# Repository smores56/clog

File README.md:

The Clog Family
===============

The Clog is a split 34-key keyboard with pinky clusters, the split version of [the
Osprette][osprette]. It grew its own revisions from there, and they all share the
same layout and firmware, so they live in one repo now, a folder per board:

- [Clog][v1] (`v1`): the original split. Pro-micro compatible, wired or bluetooth
- [Clog V2][v2] (`v2`): wireless-only, on a Seeeduino Xiao BLE, with splay and a roller
- [Clog V3][v3] (`v3`): pro-micro compatible, solder or hotswap
- [Clog V4][v4] (`v4`): hotswap with a switch plate, on a Xiao
- [Steel Toe][steel-toe] (`steel-toe`): BoardSource's V3-derived board
- [Sephirette][sephirette] (`sephirette`): MX-switch split, matching the Osprette MX

Each folder has its own README with ordering details and pictures.

Every board across both families is listed at [smores56/keyboards][index].

# Firmware

The pro-micro boards (Clog, V3, Steel Toe and Sephirette) share a matrix, so they
all run the same firmware: `clog` in QMK and the `clog` shield in ZMK. Clog V2 is
wireless-only and has its own ZMK config, and V4 runs the `geta` shield. My
personal keymaps live in [qmk_userspace][qmk_userspace] and [zmk-config][zmk-config].

# Building

Most of these boards use my [smores.pretty][smores-pretty] KiCad library as a
submodule, so clone with `--recurse-submodules`. The original Clog and the
Sephirette instead pull in Foostan's `kbd` and Daprice's `keyswitches.pretty`.

The unibody half of the family is [the Osprette][osprette].

[osprette]: https://github.com/smores56/osprette
[v1]: ./v1
[v2]: ./v2
[v3]: ./v3
[v4]: ./v4
[steel-toe]: ./steel-toe
[sephirette]: ./sephirette
[qmk_userspace]: https://github.com/smores56/qmk_userspace
[zmk-config]: https://github.com/smores56/zmk-config
[smores-pretty]: https://github.com/smores56/smores.pretty
[index]: https://github.com/smores56/keyboards

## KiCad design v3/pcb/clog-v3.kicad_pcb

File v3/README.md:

The Clog V3
===========

The Clog V3 is a 34-key split keyboard. It has the following features:

- Choc V1 switches (solder or hotswap)
- Wireless or wired only with any Pro Micro-compatible controller
- Pinky clusters (top pinky keys on the sides)
- Splay (4° between middle and ring, 8° between ring and pinky)
- SplitKB puck support for tenting

## How to Order

The [PCB gerber](./gerber/clog-v3.zip) and [plate gerber](./gerber/clog-v3-plate.zip)
have everything you'll need to get this printed.
You can order from [JLC](https://jlcpcb.com) by just uploading that ZIP archive and keeping
the default options. I'd suggest removing the order number, otherwise they'll put
one on the board somewhere randomly.

## Building

### Parts Needed

Part Name            | Quantity        | Notes                                    | Link
--------------------:|:---------------:|:----------------------------------------:|:----
PCB                  | 2 (halves)      |                                          | [JLC](https://jlcpcb.com)
Choc V1 Switches     | 34              |                                          | <https://mkultra.click/choc-switches>
Choc Keycaps         | 34              |                                          | <https://mkultra.click/mbk-factory-colors>
SMD Diodes           | 34              |                                          | <https://www.aliexpress.com/item/3256802562651339.html>
Power Switches       | 2               | Technically optional                     | <https://www.digikey.com/en/products/detail/nidec-copal-electronics/CUS-12TB/1124222>
Pro Micro Controller | 2               | Not technically optional                 | <https://www.boardsource.xyz/products/blok>
Small LiPo Batteries | 2               |                                          | <https://www.aliexpress.com/item/2251832610867849.html>
Inch of Copper Wire  | 1               | Use thin and sheathed                    | Any hardware store
MCU Sockets          | 1 strip to chop | Optional                                 | <https://www.digikey.com/en/products/detail/mill-max-manufacturing-corp/316-43-164-41-006000/1212147>
MCU Socket Pins      | 28              | Optional, buy extras, these are slippery | <https://www.digikey.com/en/products/detail/mill-max-manufacturing-corp/3320-0-00-15-00-00-03-0/4147392>

### Tips

I'd solder the parts in this order:

- Diodes
- Power switches
- MCU sockets/Headers for the Pro Micro's
- MCU pins if you're [socketing](https://docs.splitkb.com/hc/en-us/articles/360011263059-How-do-I-socket-a-microcontroller-)
- Batteries (To the +ve and -ve terminals)
- Choc switches

## Pictures

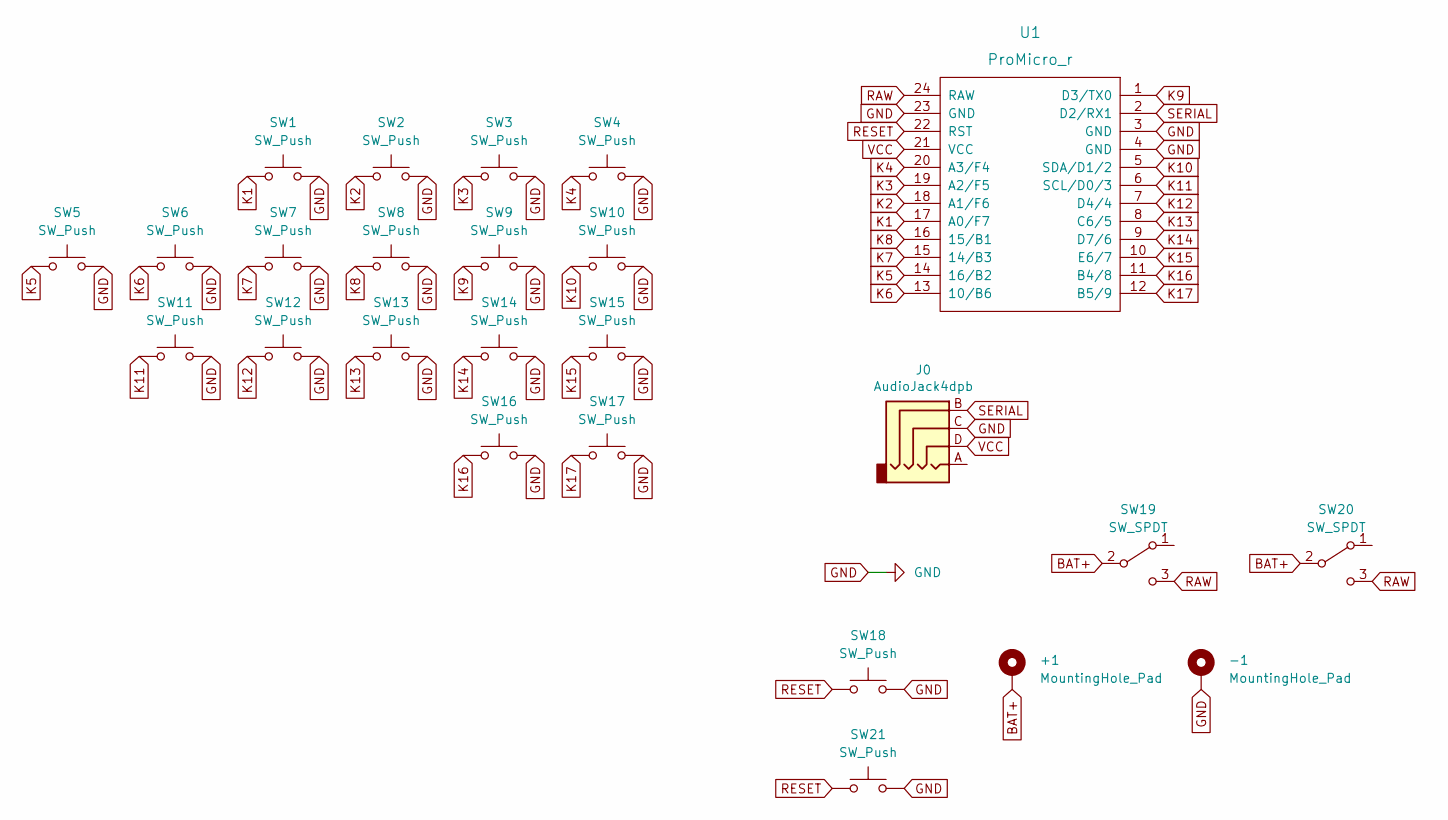
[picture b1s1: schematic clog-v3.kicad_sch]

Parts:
+1: MountingHole_Pad; single-pin
-1: MountingHole_Pad; single-pin
J0: AudioJack4dpb; trrs
SW1, SW2, SW3, SW4, SW5, SW6, SW7, SW8, SW9, SW10, SW11, SW12, SW13, SW14, SW15, SW16, SW17: SW_Push; choc-switch-socket-only
SW18, SW21: SW_Push; reset-switch-angled-4pin
SW19, SW20: SW_SPDT; power-switch
U1: ProMicro_r; pro-micro

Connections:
BAT+: +1.1, SW19.2 (B), SW20.2 (B)
GND: -1.1, J0.C, SW1.2, SW2.2, SW3.2, SW4.2, SW5.2, SW6.2, SW7.2, SW8.2, SW9.2, SW10.2, SW11.2, SW12.2, SW13.2, SW14.2, SW15.2, SW16.2, SW17.2, SW18.2, SW21.2, U1.3 (GND), U1.4 (GND), U1.23 (GND)
K1: SW1.1, U1.17 (A0/F7)
K2: SW2.1, U1.18 (A1/F6)
K3: SW3.1, U1.19 (A2/F5)
K4: SW4.1, U1.20 (A3/F4)
K5: SW5.1, U1.14 (16/B2)
K6: SW6.1, U1.13 (10/B6)
K7: SW7.1, U1.15 (14/B3)
K8: SW8.1, U1.16 (15/B1)
K9: SW9.1, U1.1 (D3/TX0)
K10: SW10.1, U1.5 (SDA/D1/2)
K11: SW11.1, U1.6 (SCL/D0/3)
K12: SW12.1, U1.7 (D4/4)
K13: SW13.1, U1.8 (C6/5)
K14: SW14.1, U1.9 (D7/6)
K15: SW15.1, U1.10 (E6/7)
K16: SW16.1, U1.11 (B4/8)
K17: SW17.1, U1.12 (B5/9)
RAW: SW19.3 (C), SW20.3 (C), U1.24 (RAW)
RESET: SW18.1, SW21.1, U1.22 (RST)
SERIAL: J0.B, U1.2 (D2/RX1)
VCC: J0.D, U1.21 (VCC)

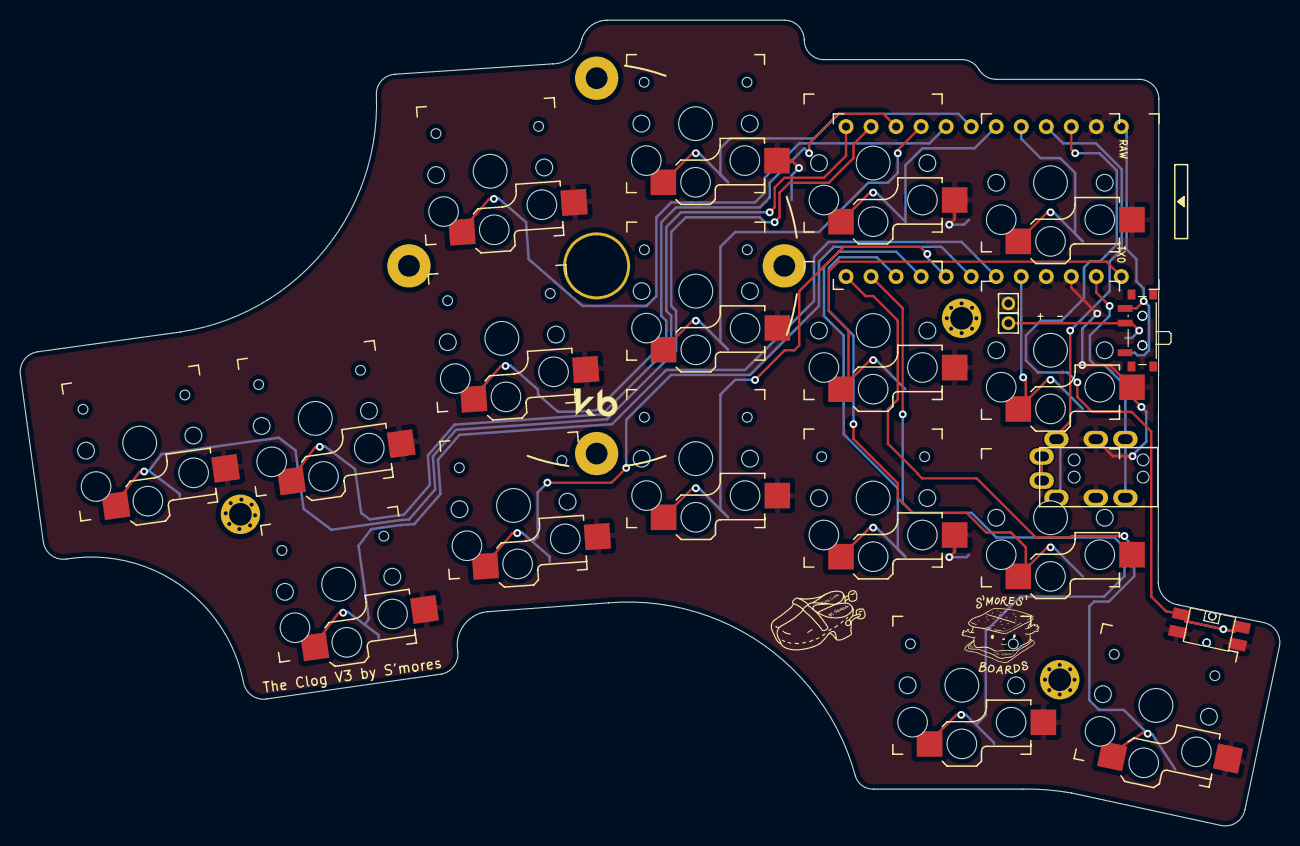
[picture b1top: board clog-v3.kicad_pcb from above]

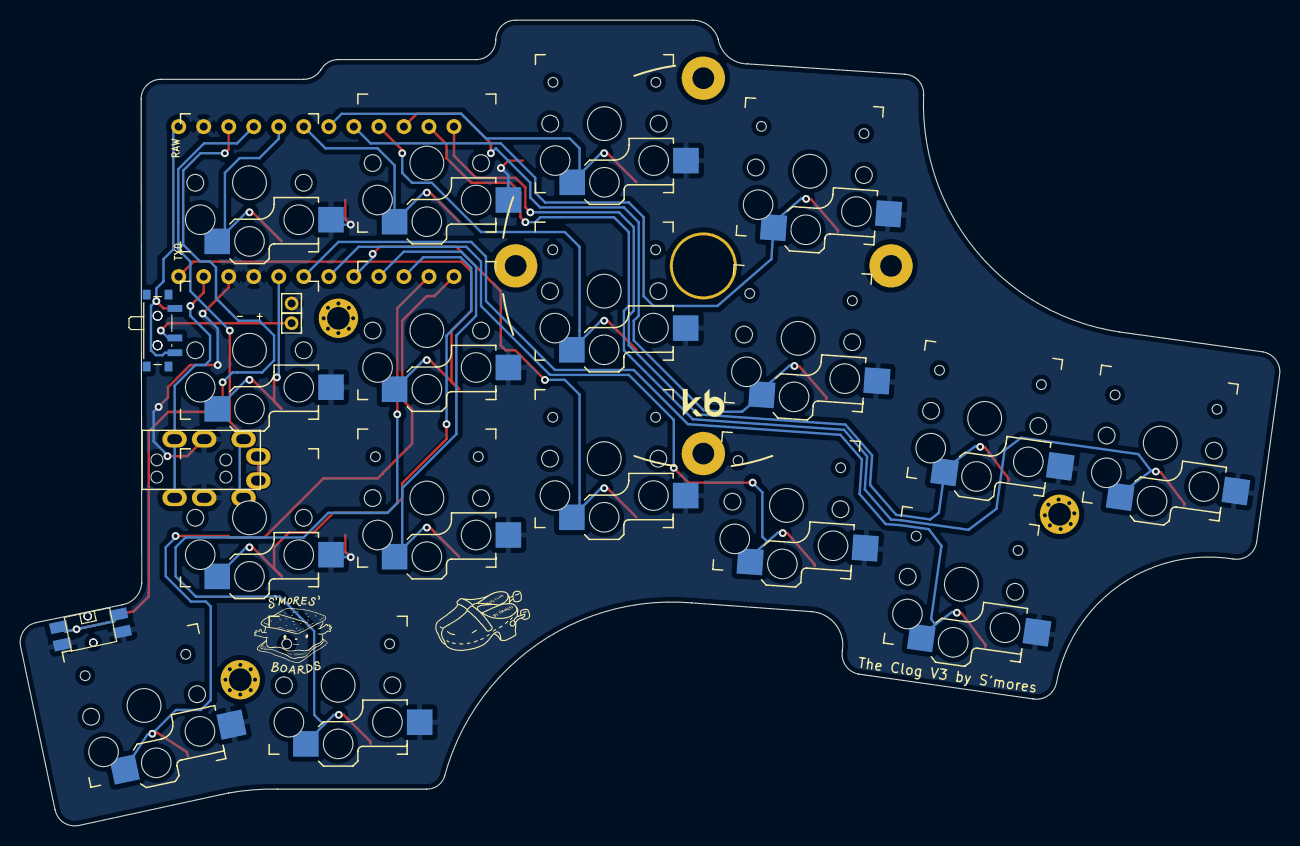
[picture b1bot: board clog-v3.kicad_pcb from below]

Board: 2 copper layers, 127.8 x 81.8 mm, 28 parts (2 on the bottom side), 23 nets.

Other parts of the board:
Ref**: Val**; m2-hole
Ref**#2, Ref**#3: Val**; m2-hole

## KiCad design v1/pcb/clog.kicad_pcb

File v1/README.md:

The Clog
========

The Clog is a split 34-key keyboard with pinky clusters. It is the split
version of the [Osprette][osprette], designed by me, which itself was inspired by
the [Balbuzard][balbuzard] by brow.

# Pictures

[osprette]: https://github.com/smores56/osprette
[balbuzard]: https://github.com/brow/balbuzard

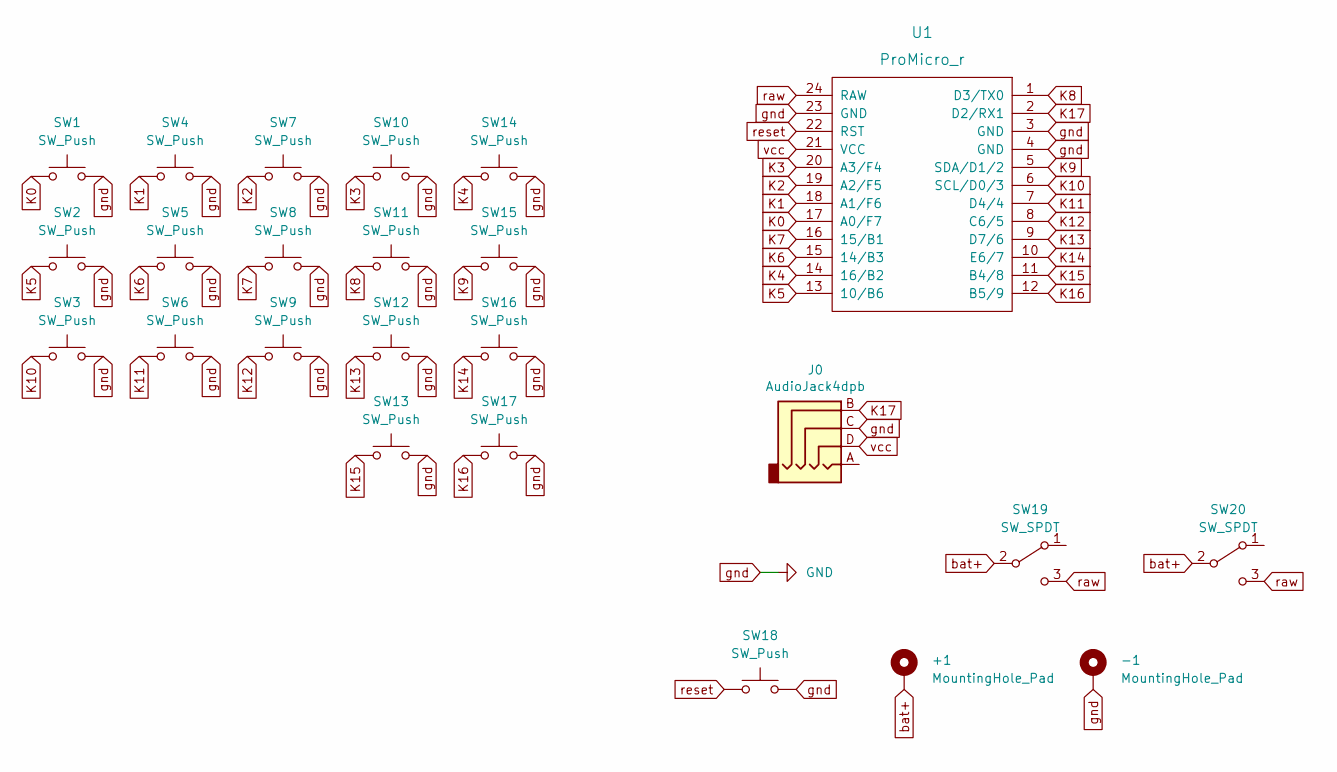
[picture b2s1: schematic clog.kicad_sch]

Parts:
+1: MountingHole_Pad; 1pin_conn
-1: MountingHole_Pad; 1pin_conn
J0: AudioJack4dpb; MJ-4PP-9
SW1, SW2, SW3, SW4, SW5, SW6, SW7, SW8, SW9, SW10, SW11, SW12, SW13, SW14, SW15, SW16, SW17: SW_Push; Kailh_socket_PG1350_optional_reversible
SW18: SW_Push; ResetSW
SW19, SW20: SW_SPDT; SW_SPDT_PCM12
U1: ProMicro_r; ProMicro_v3.5

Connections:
K0: SW1.1, U1.17 (A0/F7)
K1: SW4.1, U1.18 (A1/F6)
K2: SW7.1, U1.19 (A2/F5)
K3: SW10.1, U1.20 (A3/F4)
K4: SW14.1, U1.14 (16/B2)
K5: SW2.1, U1.13 (10/B6)
K6: SW5.1, U1.15 (14/B3)
K7: SW8.1, U1.16 (15/B1)
K8: SW11.1, U1.1 (D3/TX0)
K9: SW15.1, U1.5 (SDA/D1/2)
K10: SW3.1, U1.6 (SCL/D0/3)
K11: SW6.1, U1.7 (D4/4)
K12: SW9.1, U1.8 (C6/5)
K13: SW12.1, U1.9 (D7/6)
K14: SW16.1, U1.10 (E6/7)
K15: SW13.1, U1.11 (B4/8)
K16: SW17.1, U1.12 (B5/9)
K17: J0.B, U1.2 (D2/RX1)
bat+: +1.1, SW19.2 (B), SW20.2 (B); also elsewhere on the board
gnd: -1.1, J0.C, SW1.2, SW2.2, SW3.2, SW4.2, SW5.2, SW6.2, SW7.2, SW8.2, SW9.2, SW10.2, SW11.2, SW12.2, SW13.2, SW14.2, SW15.2, SW16.2, SW17.2, SW18.2, U1.3 (GND), U1.4 (GND), U1.23 (GND); also elsewhere on the board
raw: SW19.3 (C), SW20.3 (C), U1.24 (RAW)
reset: SW18.1, U1.22 (RST)
vcc: J0.D, U1.21 (VCC)

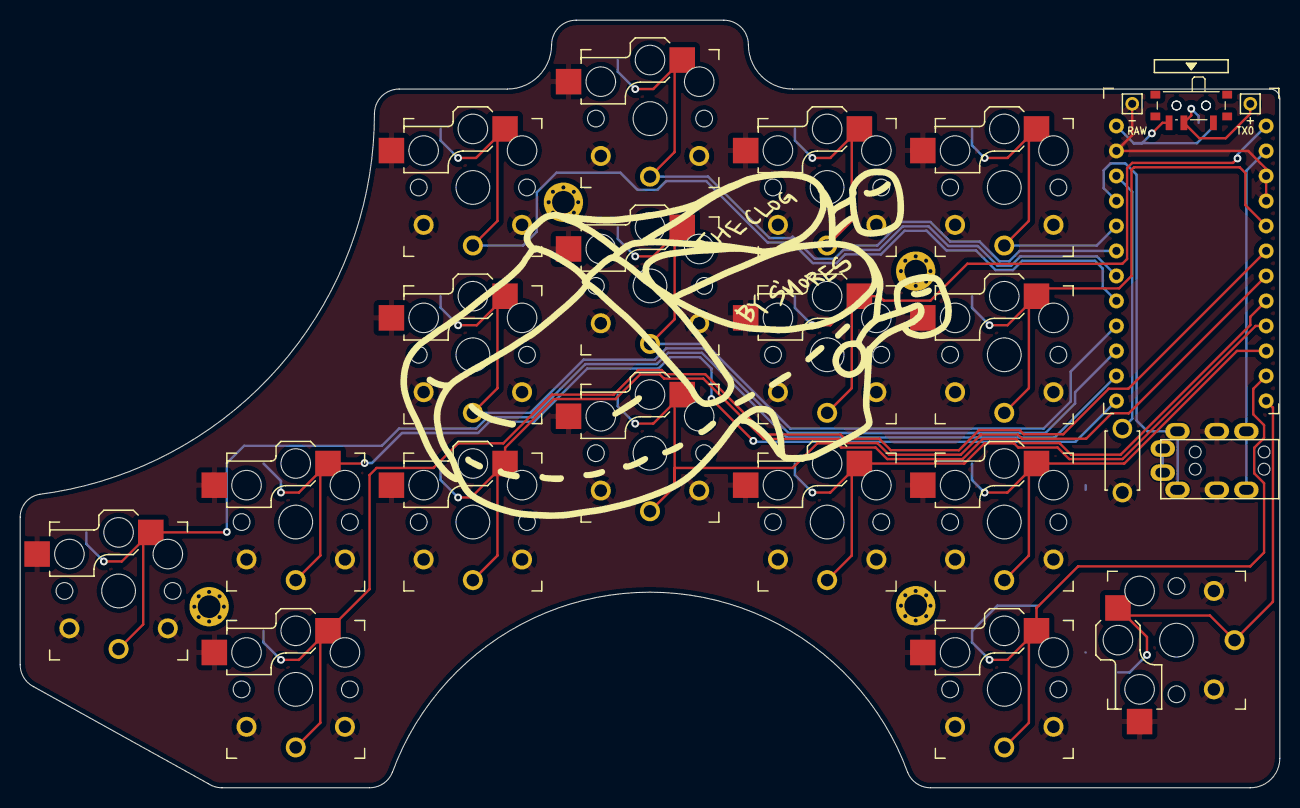
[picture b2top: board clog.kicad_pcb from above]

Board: 2 copper layers, 128.0 x 78.0 mm, 28 parts (1 on the bottom side), 23 nets.

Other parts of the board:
+: MountingHole_Pad; 1pin_conn
-: MountingHole_Pad; 1pin_conn
Ref**: Val**; M2_HOLE_v3
Ref**#2, Ref**#3, Ref**#4: Val**; M2_HOLE_v3

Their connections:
bat+: +.1; also elsewhere on the board
gnd: -.1; also elsewhere on the board

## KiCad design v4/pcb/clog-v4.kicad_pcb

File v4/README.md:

The Clog V4
===========

The Clog V4 is a 34-key split keyboard. It has the following features:

- Choc V1 switches
- Wired or wireless with Seeeduino Xiao controllers
- Pinky clusters (top pinky keys on the sides)
- Splay (4° between middle and ring and between ring and pinky)
- Hotswap with a switch plate for stability
- SplitKB puck support for tenting

## How to Order

The gerber ZIPs ([PCB](./gerber/clog-v4.zip) and [plate](./gerber/clog-v4-plate.zip))
have everything you'll need to get this printed. You can order from [JLC](https://jlcpcb.com)
by just uploading the ZIP archives and keeping the default options. I'd suggest removing
the order number, otherwise they'll put one on the boards somewhere randomly.

## Building

### Parts Needed

Part Name                  | Quantity        | Notes                                    | Link
--------------------------:|:---------------:|:----------------------------------------:|:----
PCB                        | 2 (halves)      |                                          | [JLC](https://jlcpcb.com)
Switch Plate               | 2 (halves)      |                                          | [JLC](https://jlcpcb.com)
Choc V1 Switches           | 34              |                                          | <https://mkultra.click/choc-switches>
Choc Keycaps               | 34              |                                          | <https://mkultra.click/mbk-factory-colors>
SMD Diodes                 | 34              |                                          | <https://www.aliexpress.com/item/3256802562651339.html>
Kailh Choc Hotswap Sockets | 34              |                                          | <https://mkultra.click/kailh-hotswap-sockets>
Power Switches             | 2               | optional                                 | <https://www.digikey.com/en/products/detail/nidec-copal-electronics/CUS-12TB/1124222>
Reset Switches             | 2               | optional                                 | <https://www.digikey.com/en/products/detail/e-switch/TL1014BF160QG/3910805>
Xiao (BLE)                 | 2               |                                          | <https://www.seeedstudio.com/Seeed-XIAO-BLE-nRF52840-p-5201.html>
Small LiPo Batteries       | 2               |                                          | <https://www.aliexpress.com/item/2251832610867849.html>
Inch of Copper Wire        | 1               | Use thin and sheathed                    | Any hardware store
MCU Sockets                | 1 strip to chop | Optional, chop into sections of 7 pins   | <https://www.digikey.com/en/products/detail/mill-max-manufacturing-corp/316-43-164-41-006000/1212147>
MCU Socket Pins            | 28              | Optional, buy extras, these are slippery | <https://www.digikey.com/en/products/detail/mill-max-manufacturing-corp/3320-0-00-15-00-00-03-0/4147392>

### Tips

I'd solder the parts in this order:

- Diodes
- Hotswap sockets
- Power switches
- MCU sockets/Headers that came with the Xiao's
- MCU pins if you're [socketing](https://docs.splitkb.com/hc/en-us/articles/360011263059-How-do-I-socket-a-microcontroller-)
- Batteries (To the +ve pad under the controller and to the -ve hole on the board)
- The "bodge" wire from the "Reset" hole to the reset pad under the controller

## Firmware

The V4 runs the `geta` shield in [my ZMK config][zmk-config].

## Pictures

[zmk-config]: https://github.com/smores56/zmk-config

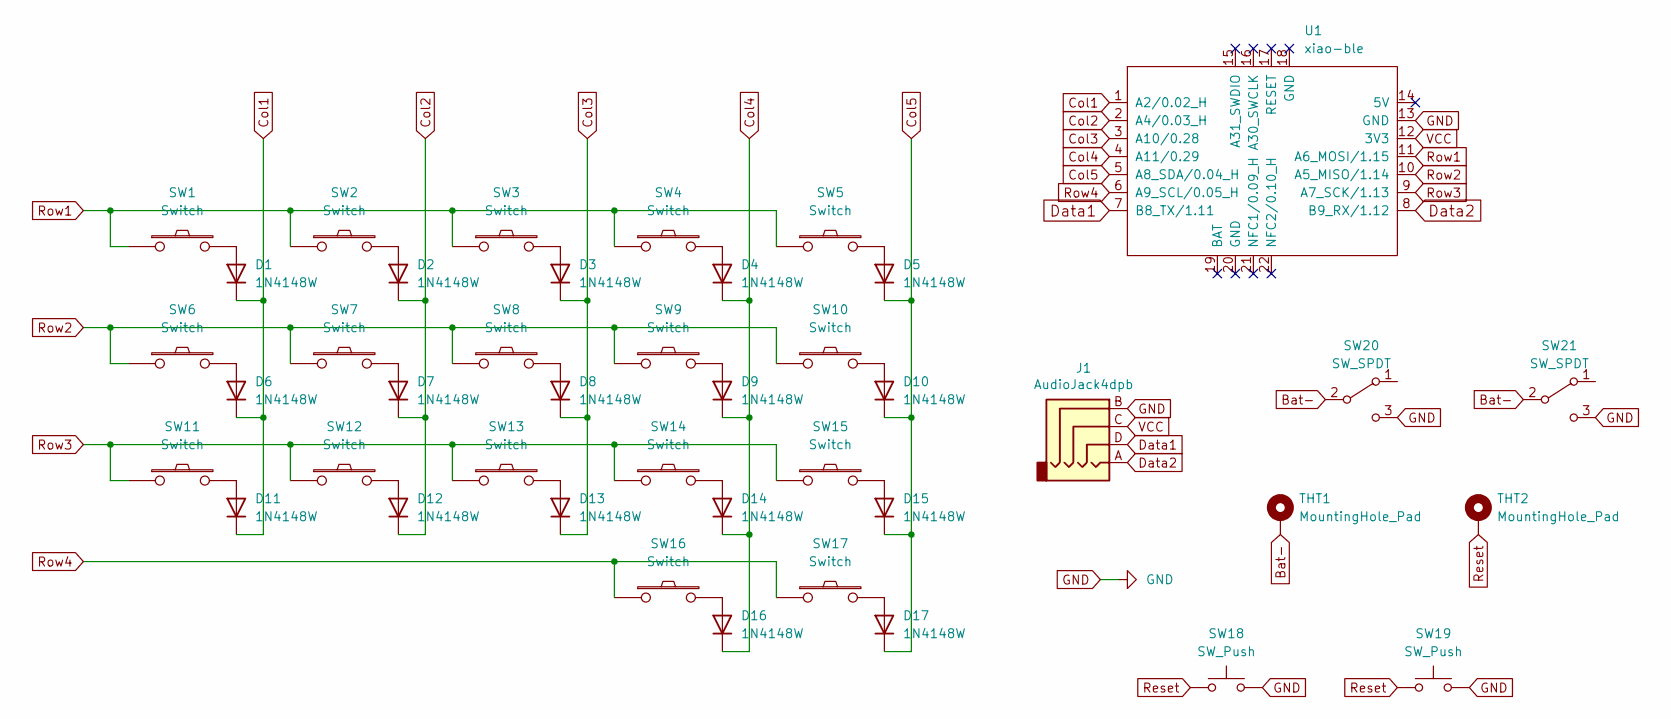
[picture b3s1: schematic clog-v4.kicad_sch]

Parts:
D1, D2, D3, D4, D5, D6, D7, D8, D9, D10, D11, D12, D13, D14, D15, D16, D17: 1N4148W; smd-diode
J1: AudioJack4dpb; trrs
SW1, SW2, SW3, SW4, SW5, SW6, SW7, SW8, SW9, SW10, SW11, SW12, SW13, SW14, SW15, SW16, SW17: Switch; choc-switch-socket-only
SW18, SW19: SW_Push; reset-switch-angled-4pin
SW20, SW21: SW_SPDT; power-switch
THT1, THT2: MountingHole_Pad; single-pin
U1: xiao-ble

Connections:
Bat-: SW20.2 (B), SW21.2 (B), THT1.1
Col1: D1.1 (K), D6.1 (K), D11.1 (K), U1.1 (A2/0.02_H)
Col2: D2.1 (K), D7.1 (K), D12.1 (K), U1.2 (A4/0.03_H)
Col3: D3.1 (K), D8.1 (K), D13.1 (K), U1.3 (A10/0.28)
Col4: D4.1 (K), D9.1 (K), D14.1 (K), D16.1 (K), U1.4 (A11/0.29)
Col5: D5.1 (K), D10.1 (K), D15.1 (K), D17.1 (K), U1.5 (A8_SDA/0.04_H)
Data1: J1.D, U1.7 (B8_TX/1.11)
Data2: J1.A, U1.8 (B9_RX/1.12)
GND: J1.B, SW18.2, SW19.2, SW20.3 (C), SW21.3 (C), U1.13 (GND)
unnamed: D1.2 (A), SW1.2
unnamed: D2.2 (A), SW2.2
unnamed: D3.2 (A), SW3.2
unnamed: D4.2 (A), SW4.2
unnamed: D5.2 (A), SW5.2
unnamed: D6.2 (A), SW6.2
unnamed: D7.2 (A), SW7.2
unnamed: D8.2 (A), SW8.2
unnamed: D9.2 (A), SW9.2
unnamed: D10.2 (A), SW10.2
unnamed: D11.2 (A), SW11.2
unnamed: D12.2 (A), SW12.2
unnamed: D13.2 (A), SW13.2
unnamed: D14.2 (A), SW14.2
unnamed: D15.2 (A), SW15.2
unnamed: D16.2 (A), SW16.2
unnamed: D17.2 (A), SW17.2
Reset: SW18.1, SW19.1, THT2.1
Row1: SW1.1, SW2.1, SW3.1, SW4.1, SW5.1, U1.11 (A6_MOSI/1.15)
Row2: SW6.1, SW7.1, SW8.1, SW9.1, SW10.1, U1.10 (A5_MISO/1.14)
Row3: SW11.1, SW12.1, SW13.1, SW14.1, SW15.1, U1.9 (A7_SCK/1.13)
Row4: SW16.1, SW17.1, U1.6 (A9_SCL/0.05_H)
VCC: J1.C, U1.12 (3V3)

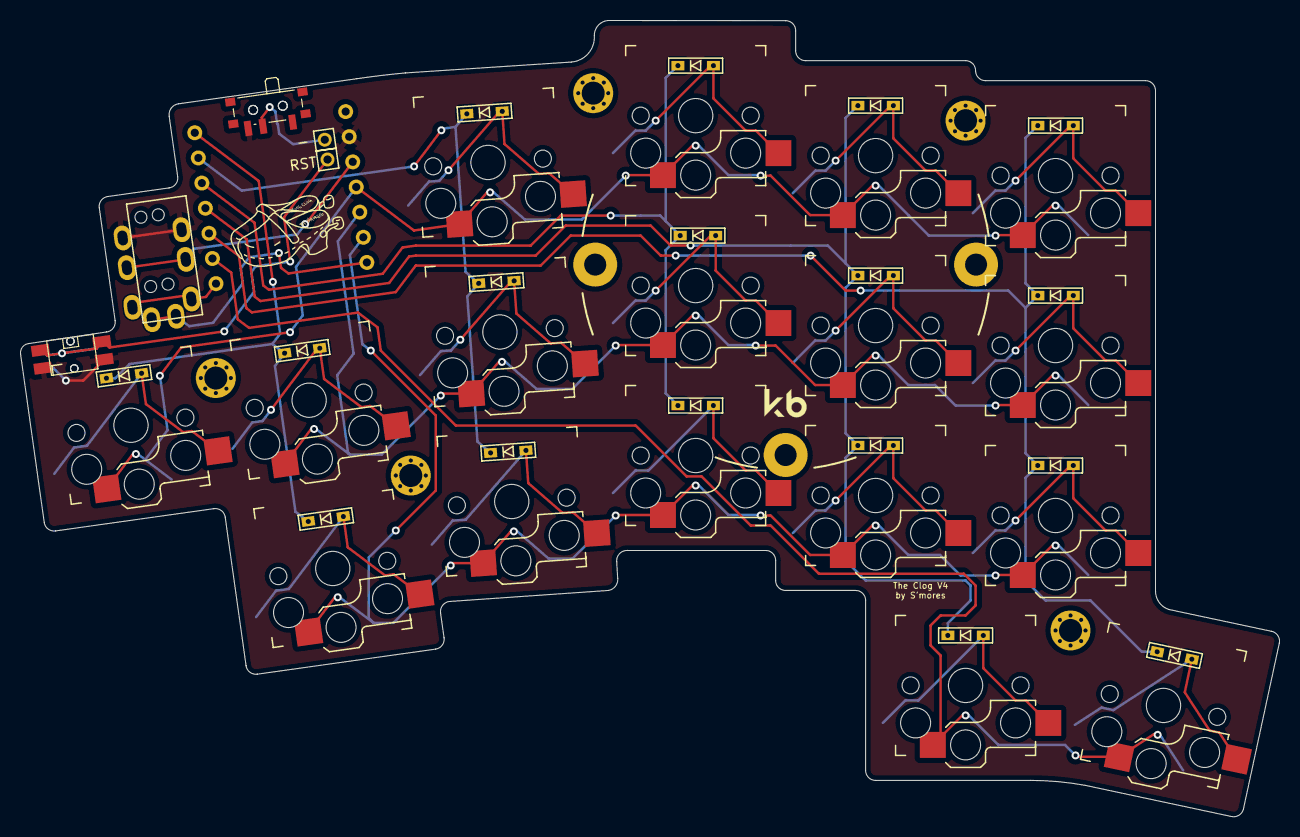
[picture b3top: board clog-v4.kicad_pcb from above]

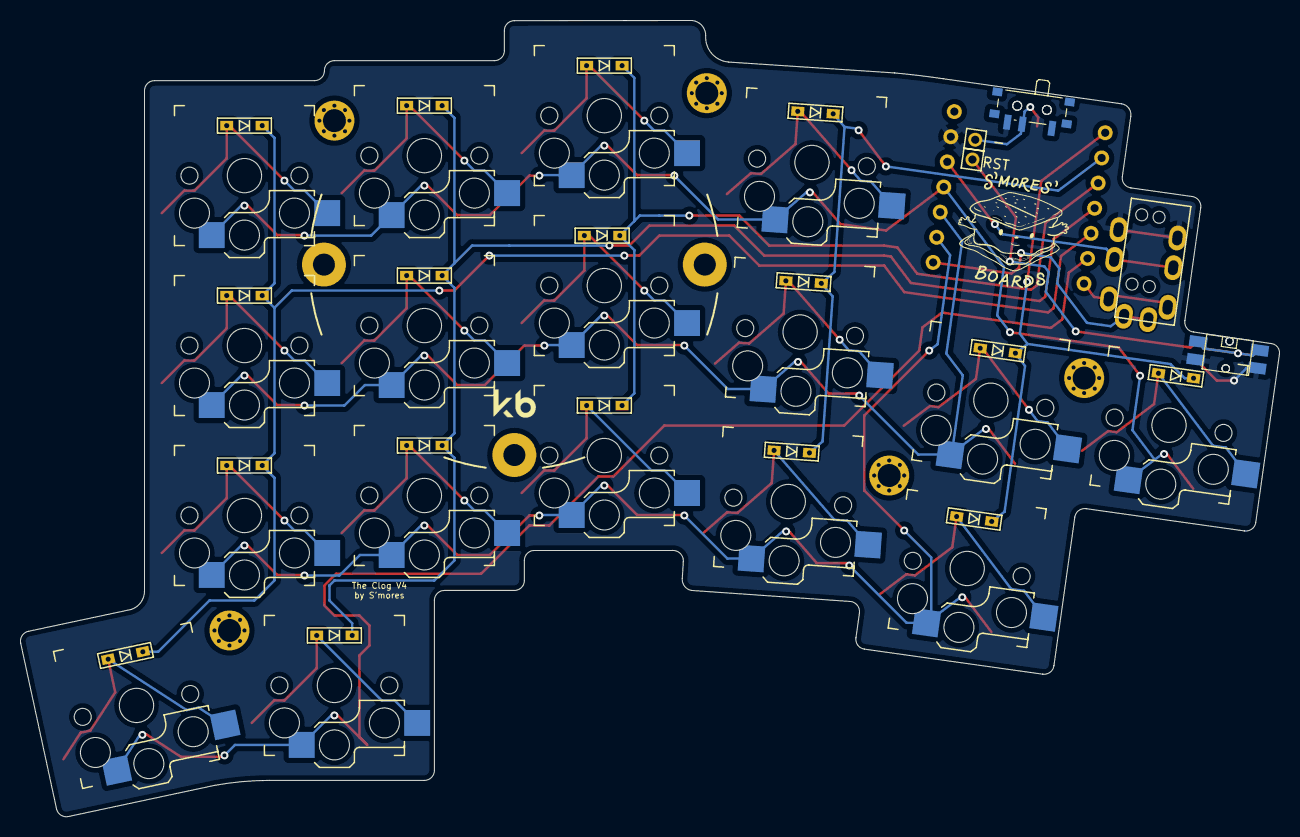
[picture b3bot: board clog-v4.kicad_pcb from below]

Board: 2 copper layers, 125.9 x 79.7 mm, 47 parts (2 on the bottom side), 32 nets.

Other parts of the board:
Ref**: Val**; m2-hole
Ref**#2, Ref**#3, Ref**#4, Ref**#5: Val**; m2-hole

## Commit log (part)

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2021-10-27 Rename to the Clog
2021-10-28 Update the art
2021-11-24 add wired split option
2021-12-25 add first case design
2021-12-26 change case angles, fix hole positioning
2022-01-16 add case variants
2022-01-16 add gitignore
2022-10-20 Make Clog Case Import Relative
